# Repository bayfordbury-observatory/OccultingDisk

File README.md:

# OccultingDisk

Sun-tracking occulting disk for all-sky camera

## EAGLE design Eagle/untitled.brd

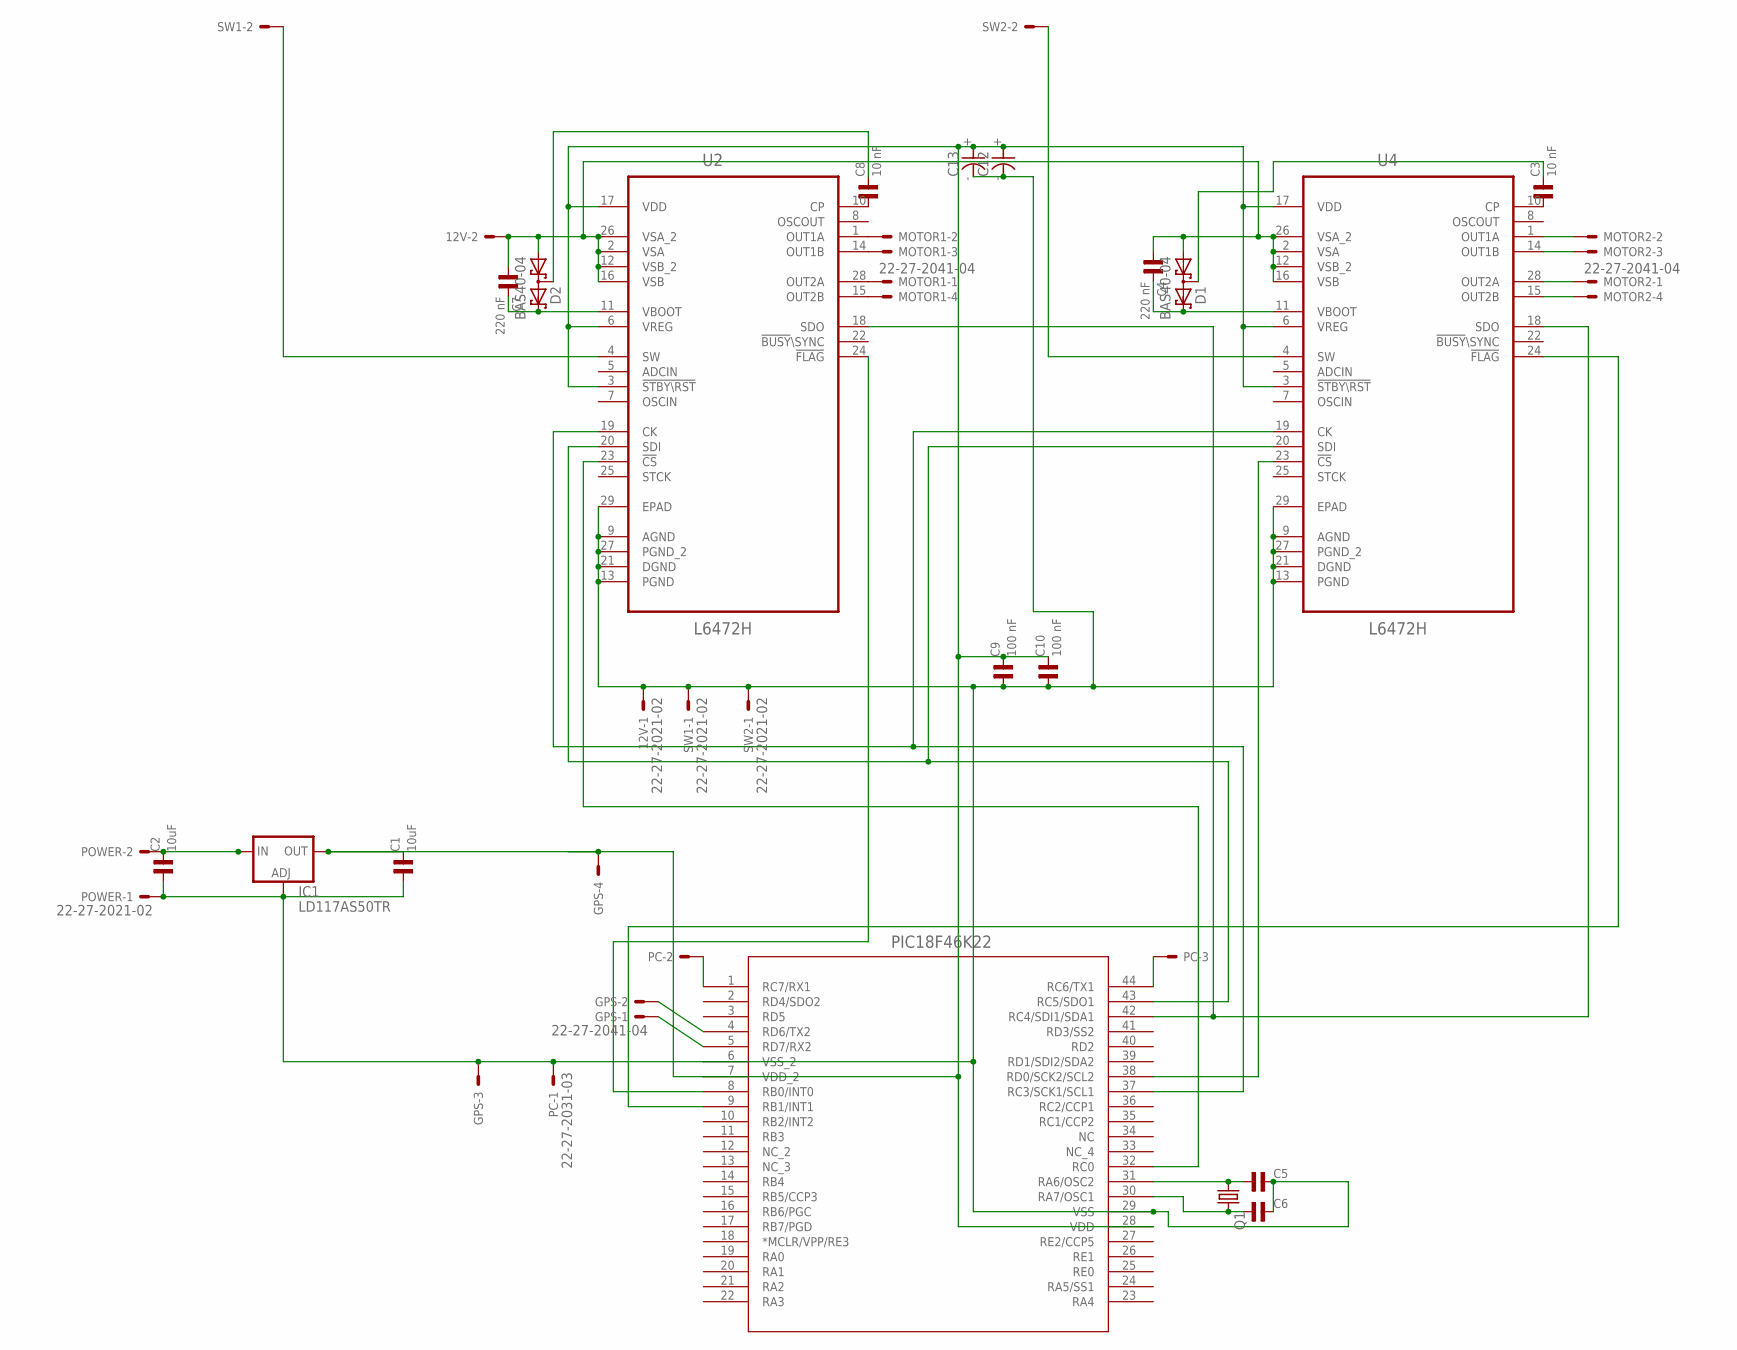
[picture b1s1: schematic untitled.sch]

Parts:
12V: 22-27-2021-02; 6410-02
C1, C2: 10uF; 0603
C3, C8: 10 nF; 0603
C4, C7: 220 nF; 0603
C5, C6: C0603; 0603
C9, C10: 100 nF; 0603
C12, C13: C7243; 7243
D1, D2: BAS40-04; SOT23
GPS: 22-27-2041-04; 6410-04
IC1: LD117AS50TR; SOT223
MOTOR1, MOTOR2: 22-27-2041-04; 6410-04
PC: 22-27-2031-03; 6410-03
POWER: 22-27-2021-02; 6410-02
Q1: CRYSTALHC49S; HC49/S
SW1, SW2: 22-27-2021-02; 6410-02
U1: PIC18F46K22-X_PT; TQFP44_10X10MC
U2, U4: L6472H; SOP65P640X120-29N

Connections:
3.3V: C1.2, C9.2, C10.2, C12.+, C13.+, GPS.4, IC1.4 (OUT), U1.7 (VDD_2), U1.28 (VDD), U2.3 (!STBY\RST), U2.6 (VREG), U2.17 (VDD), U4.3 (!STBY\RST), U4.6 (VREG), U4.17 (VDD)
12V: 12V.2, C4.1, C7.1, D1.1 (A1), D2.1 (A1), U2.2 (VSA), U2.12 (VSB_2), U2.16 (VSB), U2.26 (VSA_2), U4.2 (VSA), U4.12 (VSB_2), U4.16 (VSB), U4.26 (VSA_2)
CS1: U1.32 (RC0), U2.23 (!CS)
CS2: U1.38 (RD0/SCK2/SCL2), U4.23 (!CS)
FLAG1: U1.8 (RB0/INT0), U2.24 (!FLAG)
FLAG2: U1.9 (RB1/INT1), U4.24 (!FLAG)
GND: 12V.1, C1.1, C2.1, C5.2, C6.2, C9.1, C10.1, C12.-, C13.-, GPS.3, IC1.1 (ADJ), PC.1, POWER.1, SW1.1, SW2.1, U1.6 (VSS_2), U1.29 (VSS), U2.9 (AGND), U2.13 (PGND), U2.21 (DGND), U2.27 (PGND_2), U2.29 (EPAD), U4.9 (AGND), U4.13 (PGND), U4.21 (DGND), U4.27 (PGND_2), U4.29 (EPAD)
unnamed: C5.1, Q1.1, U1.31 (RA6/OSC2)
unnamed: C6.1, Q1.2, U1.30 (RA7/OSC1)
unnamed: C2.2, IC1.3 (IN), POWER.2
unnamed: MOTOR1.1, U2.28 (OUT2A)
unnamed: MOTOR1.2, U2.1 (OUT1A)
unnamed: MOTOR1.3, U2.14 (OUT1B)
unnamed: MOTOR1.4, U2.15 (OUT2B)
unnamed: MOTOR2.1, U4.28 (OUT2A)
unnamed: MOTOR2.2, U4.1 (OUT1A)
unnamed: MOTOR2.3, U4.14 (OUT1B)
unnamed: MOTOR2.4, U4.15 (OUT2B)
unnamed: C4.2, D1.2 (C2), U4.11 (VBOOT)
unnamed: C3.1, U4.10 (CP)
unnamed: C3.2, D1.3 (C1A2)
unnamed: SW1.2, U2.4 (SW)
unnamed: C8.1, U2.10 (CP)
unnamed: C8.2, D2.3 (C1A2)
unnamed: C7.2, D2.2 (C2), U2.11 (VBOOT)
RX1: PC.2, U1.1 (RC7/RX1)
RX2: GPS.1, U1.5 (RD7/RX2)
SCK: U1.37 (RC3/SCK1/SCL1), U2.19 (CK), U4.19 (CK)
SDI: U1.42 (RC4/SDI1/SDA1), U2.18 (SDO), U4.18 (SDO)
SDO: U1.43 (RC5/SDO1), U2.20 (SDI), U4.20 (SDI)
SW2: SW2.2, U4.4 (SW)
TX1: PC.3, U1.44 (RC6/TX1)
TX2: GPS.2, U1.4 (RD6/TX2)

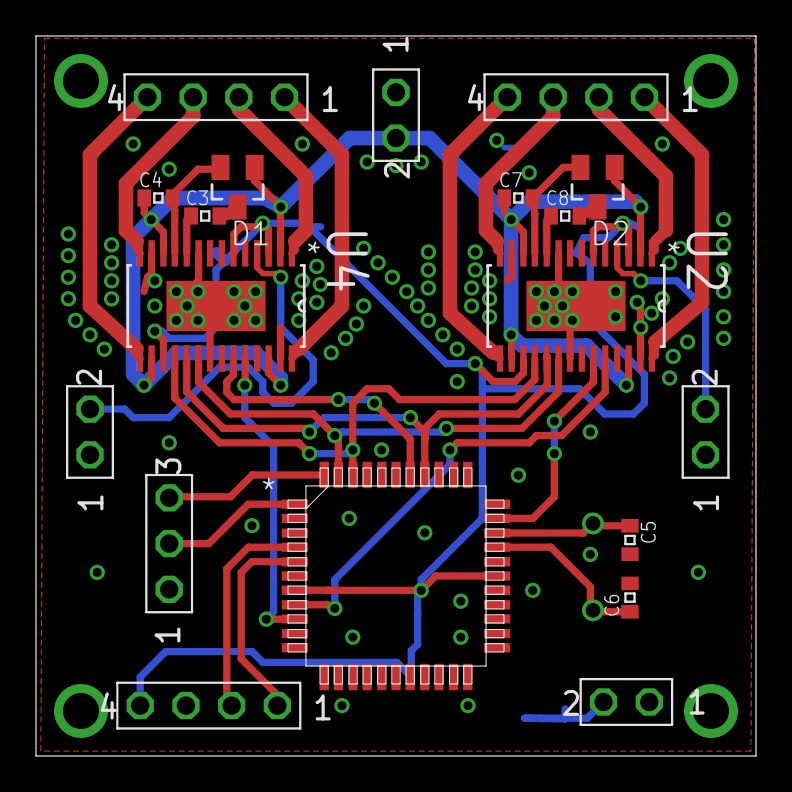
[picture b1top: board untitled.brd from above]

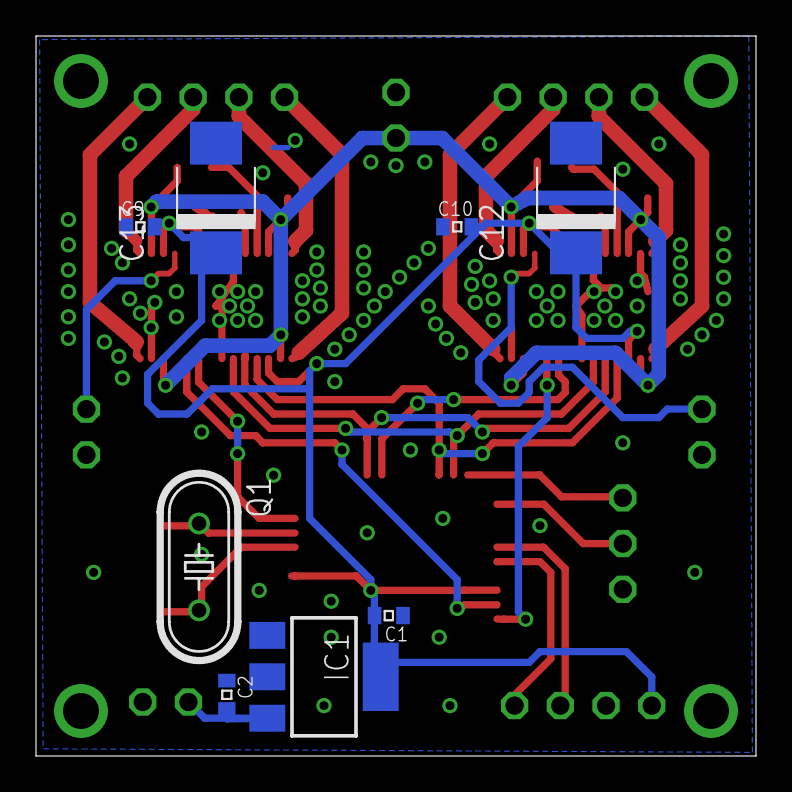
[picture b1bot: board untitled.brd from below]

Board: 2 copper layers, 40.0 x 40.0 mm, 27 parts (8 on the bottom side), 33 nets.

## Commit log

2019-05-01 Initial upload
